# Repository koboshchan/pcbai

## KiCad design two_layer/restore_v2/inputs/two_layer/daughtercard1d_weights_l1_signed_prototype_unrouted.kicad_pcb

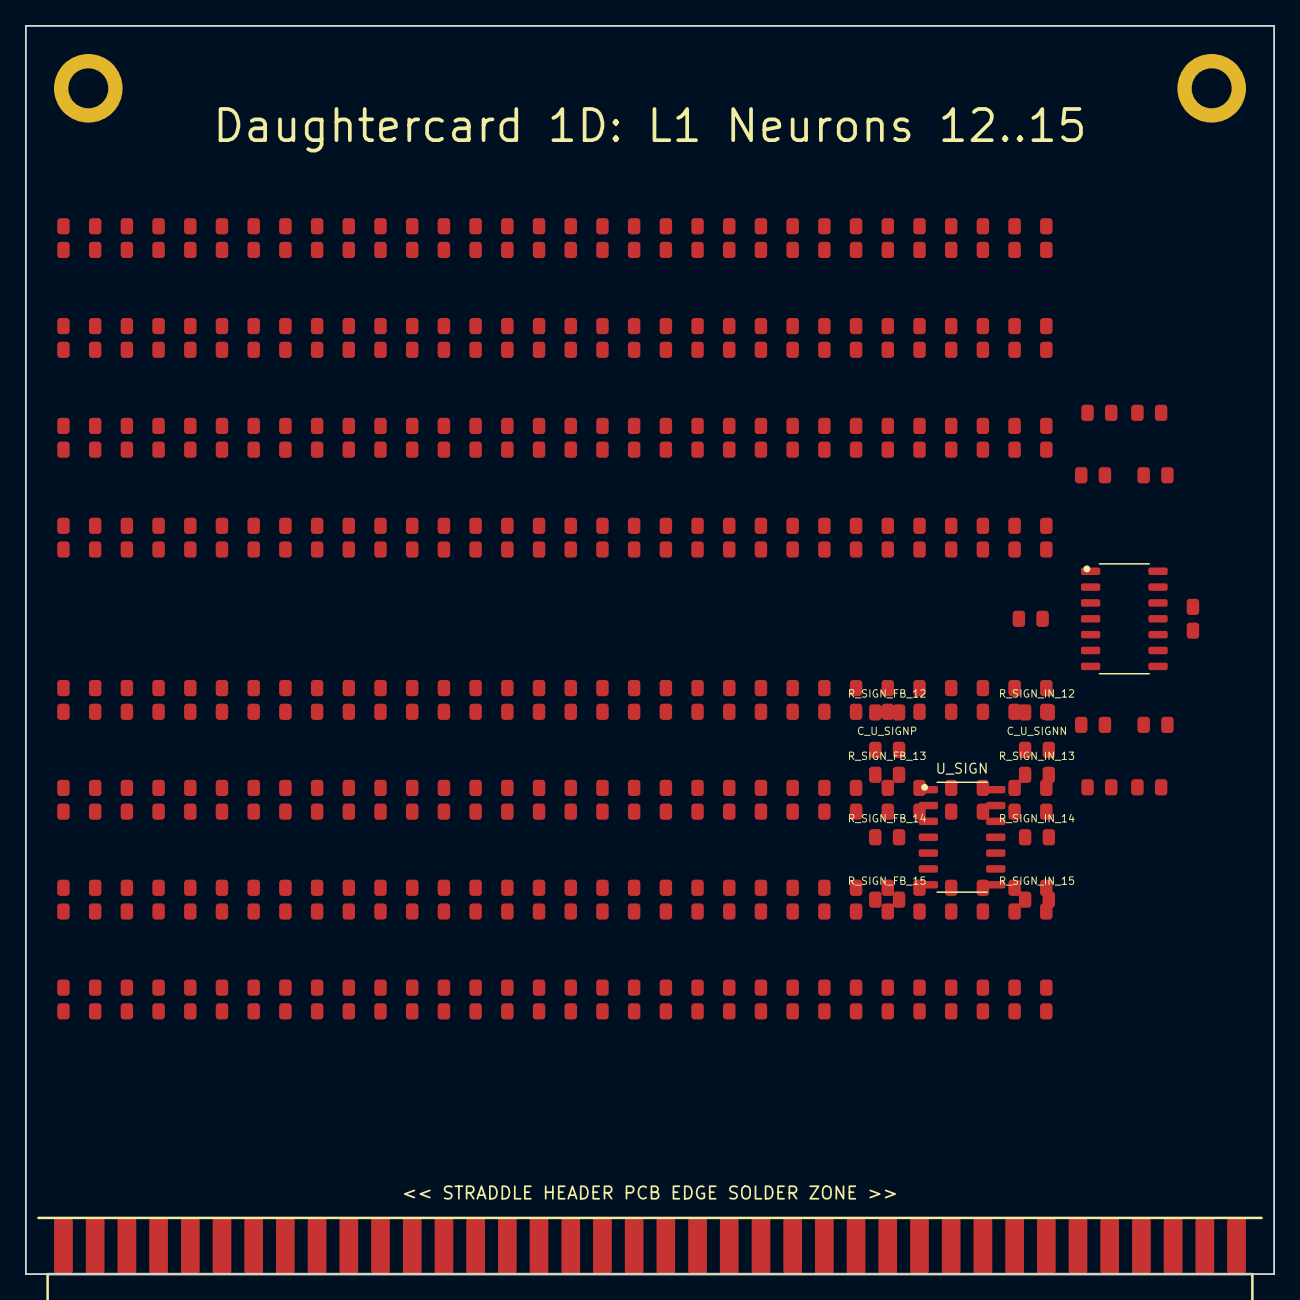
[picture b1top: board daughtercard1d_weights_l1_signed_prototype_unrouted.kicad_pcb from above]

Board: 2 copper layers, 100.0 x 100.0 mm, 281 parts (0 on the bottom side), 85 nets, no tracks yet.

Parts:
C_U1N, C_U1P: 0.1uF; C_0805_2012Metric
C_U_SIGNN: 0.1uF; C_0805_2012Metric
C_U_SIGNP: 0.1uF; C_0805_2012Metric
H1, H2: MountingHole; MountingHole_3.2mm_M3_Pad
J_STRADDLE_EDGE: PinHeader_2x38_Straddle; PinHeader_2x38_Straddle_P2.54mm
R1_0_0, R1_0_2, R1_8_2, R1_31_2, R1_56_2: 3.3k; R_0805_2012Metric
R1_0_1, R1_2_3, R1_4_0, R1_4_1, R1_7_0, R1_9_1, R1_10_1, R1_13_3, R1_18_2, R1_20_2, R1_22_0, R1_22_1, R1_26_3, R1_30_2, R1_31_1, R1_33_3, R1_35_3, R1_42_3, R1_44_3, R1_45_3, R1_52_3, R1_56_3, R1_62_3, R1_63_2: 51k; R_0805_2012Metric
R1_0_3, R1_1_1, R1_1_3, R1_5_1, R1_6_3, R1_12_3, R1_14_1, R1_16_3, R1_20_3, R1_27_3, R1_28_0, R1_30_3, R1_32_3, R1_37_3, R1_38_3, R1_40_1, R1_41_1, R1_43_3, R1_45_1, R1_48_3, R1_50_1, R1_50_3, R1_53_3, R1_54_3, R1_55_1, R1_57_1, R1_57_3, R1_58_1: 100k; R_0805_2012Metric
R1_1_0, R1_2_0, R1_10_0, R1_14_0, R1_15_0, R1_16_0, R1_17_2, R1_24_0, R1_24_2, R1_27_0, R1_37_2, R1_42_2, R1_50_0, R1_51_0, R1_57_0, R1_58_0, R1_62_0: 22k; R_0805_2012Metric
R1_1_2, R1_20_0, R1_48_0, R1_53_0, R1_55_0, R1_55_2, R1_57_2, R1_63_0: 12k; R_0805_2012Metric
R1_2_1, R1_3_3, R1_4_3, R1_5_2, R1_7_1, R1_7_2, R1_7_3, R1_9_0, R1_9_3, R1_12_1, R1_13_1, R1_15_1, R1_15_3, R1_17_0, R1_19_1, R1_21_3, R1_25_3, R1_29_1, R1_29_3, R1_32_1, R1_36_3, R1_37_1, R1_38_1, R1_41_3, R1_42_0, R1_42_1, R1_43_1, R1_43_2, R1_45_2, R1_46_3, R1_49_3, R1_55_3, R1_58_2, R1_59_1, R1_60_1, R1_61_3: 75k; R_0805_2012Metric
R1_2_2, R1_19_0, R1_25_2, R1_26_2, R1_32_0, R1_36_2, R1_60_2: 15k; R_0805_2012Metric
R1_3_0, R1_6_2, R1_8_0, R1_15_2, R1_31_0, R1_33_2, R1_35_0, R1_38_0, R1_41_2, R1_52_0, R1_59_0, R1_61_0: 18k; R_0805_2012Metric
R1_3_1, R1_6_1, R1_8_1, R1_10_3, R1_11_3, R1_12_2, R1_18_0, R1_18_1, R1_21_1, R1_21_2, R1_22_3, R1_23_1, R1_24_3, R1_25_1, R1_28_3, R1_40_0, R1_43_0, R1_46_0, R1_46_2, R1_47_3, R1_48_1, R1_49_1, R1_56_1, R1_58_3, R1_61_1: 200k; R_0805_2012Metric
R1_3_2, R1_5_0, R1_10_2, R1_11_1, R1_11_2, R1_12_0, R1_13_0, R1_20_1, R1_23_0, R1_26_0, R1_33_0, R1_37_0, R1_38_2, R1_61_2: 43k; R_0805_2012Metric
R1_4_2, R1_18_3, R1_19_3, R1_21_0, R1_30_1, R1_32_2, R1_33_1, R1_36_1, R1_39_1, R1_44_1, R1_53_1, R1_54_1, R1_63_3: 1M; R_0805_2012Metric
R1_5_3, R1_14_3, R1_19_2, R1_23_3, R1_34_1, R1_62_1, R1_63_1: 680k; R_0805_2012Metric
R1_6_0, R1_27_2, R1_35_2, R1_39_3, R1_44_0, R1_51_3, R1_60_3: 47k; R_0805_2012Metric
R1_8_3, R1_16_1, R1_17_1, R1_17_3, R1_27_1, R1_31_3, R1_40_3, R1_59_2, R1_59_3, R1_60_0: 300k; R_0805_2012Metric
R1_9_2, R1_11_0, R1_13_2, R1_14_2, R1_25_0, R1_28_2, R1_29_0, R1_29_2, R1_34_2, R1_36_0, R1_41_0, R1_44_2, R1_45_0, R1_49_0, R1_56_0: 33k; R_0805_2012Metric
R1_16_2, R1_39_2, R1_51_2: 5.6k; R_0805_2012Metric
R1_22_2, R1_35_1, R1_46_1, R1_52_1: 390k; R_0805_2012Metric
R1_23_2: 4.7k; R_0805_2012Metric
R1_24_1, R1_26_1, R1_28_1, R1_30_0, R1_47_1, R1_51_1: 470k; R_0805_2012Metric
R1_34_0, R1_39_0, R1_40_2, R1_62_2: 20k; R_0805_2012Metric
R1_34_3: DNP; R_0805_2012Metric
R1_47_0, R1_48_2, R1_54_0: 10k; R_0805_2012Metric
R1_47_2, R1_49_2, R1_50_2, R1_52_2, R1_53_2, R1_54_2: 7.5k; R_0805_2012Metric
R_SIGN_FB_12, R_SIGN_FB_13, R_SIGN_FB_14, R_SIGN_FB_15: 1.2k; R_0805_2012Metric
R_SIGN_IN_12, R_SIGN_IN_13, R_SIGN_IN_14, R_SIGN_IN_15: 1.2k; R_0805_2012Metric
Rb_N12: 51k; R_0805_2012Metric
Rb_N13: 300k; R_0805_2012Metric
Rb_N14: 18k; R_0805_2012Metric
Rb_N15: 390k; R_0805_2012Metric
Rf_N12, Rf_N13, Rf_N14, Rf_N15: 10k; R_0805_2012Metric
U1: TL074; SOIC-14_3.9x8.7mm_P1.27mm
U_SIGN: TL074; SOIC-14_3.9x8.7mm_P1.27mm

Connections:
+5V_REF: J_STRADDLE_EDGE.B35, Rb_N12.2, Rb_N14.2
+12V: C_U1P.2, C_U_SIGNP.1, J_STRADDLE_EDGE.B33, J_STRADDLE_EDGE.B34, U1.4, U_SIGN.4
-5V_REF: J_STRADDLE_EDGE.B36, Rb_N13.2, Rb_N15.2
-12V: C_U1N.1, C_U_SIGNN.1, J_STRADDLE_EDGE.B37, J_STRADDLE_EDGE.B38, U1.11, U_SIGN.11
GND: C_U1N.2, C_U1P.1, C_U_SIGNN.2, C_U_SIGNP.2, H1.1, H2.1, J_STRADDLE_EDGE.A37, J_STRADDLE_EDGE.A38, U1.3, U1.5, U1.10, U1.12, U_SIGN.3, U_SIGN.5, U_SIGN.10, U_SIGN.12
INV_N12: R1_7_0.2, R1_8_0.2, R1_15_0.2, R1_21_0.2, R1_22_0.2, R1_24_0.2, R1_25_0.2, R1_26_0.2, R1_27_0.2, R1_30_0.2, R1_33_0.2, R1_34_0.2, R1_35_0.2, R1_36_0.2, R1_39_0.2, R1_40_0.2, R1_41_0.2, R1_42_0.2, R1_43_0.2, R1_44_0.2, R1_45_0.2, R1_46_0.2, R1_48_0.2, R1_49_0.2, R1_50_0.2, R1_51_0.2, R1_52_0.2, R1_53_0.2, R1_54_0.2, R1_55_0.2, R1_57_0.2, R1_58_0.2, R1_59_0.2, R1_60_0.2, R1_61_0.2, R1_62_0.2, R1_63_0.2, R_SIGN_IN_12.2, Rb_N12.1, Rf_N12.2, U1.2
INV_N13: R1_8_1.2, R1_17_1.2, R1_26_1.2, R1_27_1.2, R1_30_1.2, R1_33_1.2, R1_34_1.2, R1_35_1.2, R1_39_1.2, R1_53_1.2, R1_54_1.2, R1_55_1.2, R1_62_1.2, R_SIGN_IN_13.2, Rb_N13.1, Rf_N13.2, U1.6
INV_N14: R1_1_2.2, R1_2_2.2, R1_3_2.2, R1_5_2.2, R1_6_2.2, R1_8_2.2, R1_9_2.2, R1_10_2.2, R1_11_2.2, R1_12_2.2, R1_13_2.2, R1_14_2.2, R1_15_2.2, R1_18_2.2, R1_20_2.2, R1_21_2.2, R1_24_2.2, R1_25_2.2, R1_26_2.2, R1_27_2.2, R1_28_2.2, R1_29_2.2, R1_30_2.2, R1_32_2.2, R1_33_2.2, R1_34_2.2, R1_35_2.2, R1_36_2.2, R1_37_2.2, R1_38_2.2, R1_43_2.2, R1_44_2.2, R1_45_2.2, R1_56_2.2, R1_57_2.2, R1_58_2.2, R1_59_2.2, R1_63_2.2, R_SIGN_IN_14.2, Rb_N14.1, Rf_N14.1, U1.9
INV_N15: R1_1_3.2, R1_8_3.2, R1_18_3.2, R1_19_3.2, R1_34_3.2, R1_47_3.2, R1_55_3.2, R1_63_3.2, R_SIGN_IN_15.2, Rb_N15.1, Rf_N15.1, U1.13
IN_0: J_STRADDLE_EDGE.A1, R1_0_0.1, R1_0_1.1, R1_0_2.1, R1_0_3.1
IN_1: J_STRADDLE_EDGE.A2, R1_1_0.1, R1_1_1.1, R1_1_2.1, R1_1_3.1
IN_2: J_STRADDLE_EDGE.A3, R1_2_0.1, R1_2_1.1, R1_2_2.1, R1_2_3.1
IN_3: J_STRADDLE_EDGE.A4, R1_3_0.1, R1_3_1.1, R1_3_2.1, R1_3_3.1
IN_4: J_STRADDLE_EDGE.A5, R1_4_0.1, R1_4_1.1, R1_4_2.1, R1_4_3.1
IN_5: J_STRADDLE_EDGE.A6, R1_5_0.1, R1_5_1.1, R1_5_2.1, R1_5_3.1
IN_6: J_STRADDLE_EDGE.A7, R1_6_0.1, R1_6_1.1, R1_6_2.1, R1_6_3.1
IN_7: J_STRADDLE_EDGE.A8, R1_7_0.1, R1_7_1.1, R1_7_2.1, R1_7_3.1
IN_8: J_STRADDLE_EDGE.A9, R1_8_0.1, R1_8_1.1, R1_8_2.1, R1_8_3.1
IN_9: J_STRADDLE_EDGE.A10, R1_9_0.1, R1_9_1.1, R1_9_2.1, R1_9_3.1
IN_10: J_STRADDLE_EDGE.A11, R1_10_0.1, R1_10_1.1, R1_10_2.1, R1_10_3.1
IN_11: J_STRADDLE_EDGE.A12, R1_11_0.1, R1_11_1.1, R1_11_2.1, R1_11_3.1
IN_12: J_STRADDLE_EDGE.A13, R1_12_0.1, R1_12_1.1, R1_12_2.1, R1_12_3.1
IN_13: J_STRADDLE_EDGE.A14, R1_13_0.1, R1_13_1.1, R1_13_2.1, R1_13_3.1
IN_14: J_STRADDLE_EDGE.A15, R1_14_0.1, R1_14_1.1, R1_14_2.1, R1_14_3.1
IN_15: J_STRADDLE_EDGE.A16, R1_15_0.1, R1_15_1.1, R1_15_2.1, R1_15_3.1
IN_16: J_STRADDLE_EDGE.A17, R1_16_0.1, R1_16_1.1, R1_16_2.1, R1_16_3.1
IN_17: J_STRADDLE_EDGE.A18, R1_17_0.1, R1_17_1.1, R1_17_2.1, R1_17_3.1
IN_18: J_STRADDLE_EDGE.A19, R1_18_0.1, R1_18_1.1, R1_18_2.1, R1_18_3.1
IN_19: J_STRADDLE_EDGE.A20, R1_19_0.1, R1_19_1.1, R1_19_2.1, R1_19_3.1
IN_20: J_STRADDLE_EDGE.A21, R1_20_0.1, R1_20_1.1, R1_20_2.1, R1_20_3.1
IN_21: J_STRADDLE_EDGE.A22, R1_21_0.1, R1_21_1.1, R1_21_2.1, R1_21_3.1
IN_22: J_STRADDLE_EDGE.A23, R1_22_0.1, R1_22_1.1, R1_22_2.1, R1_22_3.1
IN_23: J_STRADDLE_EDGE.A24, R1_23_0.1, R1_23_1.1, R1_23_2.1, R1_23_3.1
IN_24: J_STRADDLE_EDGE.A25, R1_24_0.1, R1_24_1.1, R1_24_2.1, R1_24_3.1
IN_25: J_STRADDLE_EDGE.A26, R1_25_0.1, R1_25_1.1, R1_25_2.1, R1_25_3.1
IN_26: J_STRADDLE_EDGE.A27, R1_26_0.1, R1_26_1.1, R1_26_2.1, R1_26_3.1
IN_27: J_STRADDLE_EDGE.A28, R1_27_0.1, R1_27_1.1, R1_27_2.1, R1_27_3.1
IN_28: J_STRADDLE_EDGE.A29, R1_28_0.1, R1_28_1.1, R1_28_2.1, R1_28_3.1
IN_29: J_STRADDLE_EDGE.A30, R1_29_0.1, R1_29_1.1, R1_29_2.1, R1_29_3.1
IN_30: J_STRADDLE_EDGE.A31, R1_30_0.1, R1_30_1.1, R1_30_2.1, R1_30_3.1
IN_31: J_STRADDLE_EDGE.A32, R1_31_0.1, R1_31_1.1, R1_31_2.1, R1_31_3.1
IN_32: J_STRADDLE_EDGE.B1, R1_32_0.1, R1_32_1.1, R1_32_2.1, R1_32_3.1
IN_33: J_STRADDLE_EDGE.B2, R1_33_0.1, R1_33_1.1, R1_33_2.1, R1_33_3.1
IN_34: J_STRADDLE_EDGE.B3, R1_34_0.1, R1_34_1.1, R1_34_2.1, R1_34_3.1
IN_35: J_STRADDLE_EDGE.B4, R1_35_0.1, R1_35_1.1, R1_35_2.1, R1_35_3.1
IN_36: J_STRADDLE_EDGE.B5, R1_36_0.1, R1_36_1.1, R1_36_2.1, R1_36_3.1
IN_37: J_STRADDLE_EDGE.B6, R1_37_0.1, R1_37_1.1, R1_37_2.1, R1_37_3.1
IN_38: J_STRADDLE_EDGE.B7, R1_38_0.1, R1_38_1.1, R1_38_2.1, R1_38_3.1
IN_39: J_STRADDLE_EDGE.B8, R1_39_0.1, R1_39_1.1, R1_39_2.1, R1_39_3.1
IN_40: J_STRADDLE_EDGE.B9, R1_40_0.1, R1_40_1.1, R1_40_2.1, R1_40_3.1
IN_41: J_STRADDLE_EDGE.B10, R1_41_0.1, R1_41_1.1, R1_41_2.1, R1_41_3.1
IN_42: J_STRADDLE_EDGE.B11, R1_42_0.1, R1_42_1.1, R1_42_2.1, R1_42_3.1
IN_43: J_STRADDLE_EDGE.B12, R1_43_0.1, R1_43_1.1, R1_43_2.1, R1_43_3.1
IN_44: J_STRADDLE_EDGE.B13, R1_44_0.1, R1_44_1.1, R1_44_2.1, R1_44_3.1
IN_45: J_STRADDLE_EDGE.B14, R1_45_0.1, R1_45_1.1, R1_45_2.1, R1_45_3.1
IN_46: J_STRADDLE_EDGE.B15, R1_46_0.1, R1_46_1.1, R1_46_2.1, R1_46_3.1
IN_47: J_STRADDLE_EDGE.B16, R1_47_0.1, R1_47_1.1, R1_47_2.1, R1_47_3.1
IN_48: J_STRADDLE_EDGE.B17, R1_48_0.1, R1_48_1.1, R1_48_2.1, R1_48_3.1
IN_49: J_STRADDLE_EDGE.B18, R1_49_0.1, R1_49_1.1, R1_49_2.1, R1_49_3.1
IN_50: J_STRADDLE_EDGE.B19, R1_50_0.1, R1_50_1.1, R1_50_2.1, R1_50_3.1
IN_51: J_STRADDLE_EDGE.B20, R1_51_0.1, R1_51_1.1, R1_51_2.1, R1_51_3.1
IN_52: J_STRADDLE_EDGE.B21, R1_52_0.1, R1_52_1.1, R1_52_2.1, R1_52_3.1
IN_53: J_STRADDLE_EDGE.B22, R1_53_0.1, R1_53_1.1, R1_53_2.1, R1_53_3.1
IN_54: J_STRADDLE_EDGE.B23, R1_54_0.1, R1_54_1.1, R1_54_2.1, R1_54_3.1
IN_55: J_STRADDLE_EDGE.B24, R1_55_0.1, R1_55_1.1, R1_55_2.1, R1_55_3.1
IN_56: J_STRADDLE_EDGE.B25, R1_56_0.1, R1_56_1.1, R1_56_2.1, R1_56_3.1
IN_57: J_STRADDLE_EDGE.B26, R1_57_0.1, R1_57_1.1, R1_57_2.1, R1_57_3.1
IN_58: J_STRADDLE_EDGE.B27, R1_58_0.1, R1_58_1.1, R1_58_2.1, R1_58_3.1
IN_59: J_STRADDLE_EDGE.B28, R1_59_0.1, R1_59_1.1, R1_59_2.1, R1_59_3.1
IN_60: J_STRADDLE_EDGE.B29, R1_60_0.1, R1_60_1.1, R1_60_2.1, R1_60_3.1
IN_61: J_STRADDLE_EDGE.B30, R1_61_0.1, R1_61_1.1, R1_61_2.1, R1_61_3.1
IN_62: J_STRADDLE_EDGE.B31, R1_62_0.1, R1_62_1.1, R1_62_2.1, R1_62_3.1
IN_63: J_STRADDLE_EDGE.B32, R1_63_0.1, R1_63_1.1, R1_63_2.1, R1_63_3.1
NEG_GROUP_12: R_SIGN_FB_12.1, R_SIGN_IN_12.1, U_SIGN.1
NEG_GROUP_13: R_SIGN_FB_13.1, R_SIGN_IN_13.1, U_SIGN.7
NEG_GROUP_14: R_SIGN_FB_14.1, R_SIGN_IN_14.1, U_SIGN.8
NEG_GROUP_15: R_SIGN_FB_15.1, R_SIGN_IN_15.1, U_SIGN.14
NEG_INV_12: R1_0_0.2, R1_1_0.2, R1_2_0.2, R1_3_0.2, R1_4_0.2, R1_5_0.2, R1_6_0.2, R1_9_0.2, R1_10_0.2, R1_11_0.2, R1_12_0.2, R1_13_0.2, R1_14_0.2, R1_16_0.2, R1_17_0.2, R1_18_0.2, R1_19_0.2, R1_20_0.2, R1_23_0.2, R1_28_0.2, R1_29_0.2, R1_31_0.2, R1_32_0.2, R1_37_0.2, R1_38_0.2, R1_47_0.2, R1_56_0.2, R_SIGN_FB_12.2, U_SIGN.2
NEG_INV_13: R1_0_1.2, R1_1_1.2, R1_2_1.2, R1_3_1.2, R1_4_1.2, R1_5_1.2, R1_6_1.2, R1_7_1.2, R1_9_1.2, R1_10_1.2, R1_11_1.2, R1_12_1.2, R1_13_1.2, R1_14_1.2, R1_15_1.2, R1_16_1.2, R1_18_1.2, R1_19_1.2, R1_20_1.2, R1_21_1.2, R1_22_1.2, R1_23_1.2, R1_24_1.2, R1_25_1.2, R1_28_1.2, R1_29_1.2, R1_31_1.2, R1_32_1.2, R1_36_1.2, R1_37_1.2, R1_38_1.2, R1_40_1.2, R1_41_1.2, R1_42_1.2, R1_43_1.2, R1_44_1.2, R1_45_1.2, R1_46_1.2, R1_47_1.2, R1_48_1.2, R1_49_1.2, R1_50_1.2, R1_51_1.2, R1_52_1.2, R1_56_1.2, R1_57_1.2, R1_58_1.2, R1_59_1.2, R1_60_1.2, R1_61_1.2, R1_63_1.2, R_SIGN_FB_13.2, U_SIGN.6
NEG_INV_14: R1_0_2.2, R1_4_2.2, R1_7_2.2, R1_16_2.2, R1_17_2.2, R1_19_2.2, R1_22_2.2, R1_23_2.2, R1_31_2.2, R1_39_2.2, R1_40_2.2, R1_41_2.2, R1_42_2.2, R1_46_2.2, R1_47_2.2, R1_48_2.2, R1_49_2.2, R1_50_2.2, R1_51_2.2, R1_52_2.2, R1_53_2.2, R1_54_2.2, R1_55_2.2, R1_60_2.2, R1_61_2.2, R1_62_2.2, R_SIGN_FB_14.2, U_SIGN.9
NEG_INV_15: R1_0_3.2, R1_2_3.2, R1_3_3.2, R1_4_3.2, R1_5_3.2, R1_6_3.2, R1_7_3.2, R1_9_3.2, R1_10_3.2, R1_11_3.2, R1_12_3.2, R1_13_3.2, R1_14_3.2, R1_15_3.2, R1_16_3.2, R1_17_3.2, R1_20_3.2, R1_21_3.2, R1_22_3.2, R1_23_3.2, R1_24_3.2, R1_25_3.2, R1_26_3.2, R1_27_3.2, R1_28_3.2, R1_29_3.2, R1_30_3.2, R1_31_3.2, R1_32_3.2, R1_33_3.2, R1_35_3.2, R1_36_3.2, R1_37_3.2, R1_38_3.2, R1_39_3.2, R1_40_3.2, R1_41_3.2, R1_42_3.2, R1_43_3.2, R1_44_3.2, R1_45_3.2, R1_46_3.2, R1_48_3.2, R1_49_3.2, R1_50_3.2, R1_51_3.2, R1_52_3.2, R1_53_3.2, R1_54_3.2, R1_56_3.2, R1_57_3.2, R1_58_3.2, R1_59_3.2, R1_60_3.2, R1_61_3.2, R1_62_3.2, R_SIGN_FB_15.2, U_SIGN.13
V_SUM_12: J_STRADDLE_EDGE.A33, Rf_N12.1, U1.1
V_SUM_13: J_STRADDLE_EDGE.A34, Rf_N13.1, U1.7
V_SUM_14: J_STRADDLE_EDGE.A35, Rf_N14.2, U1.8
V_SUM_15: J_STRADDLE_EDGE.A36, Rf_N15.2, U1.14

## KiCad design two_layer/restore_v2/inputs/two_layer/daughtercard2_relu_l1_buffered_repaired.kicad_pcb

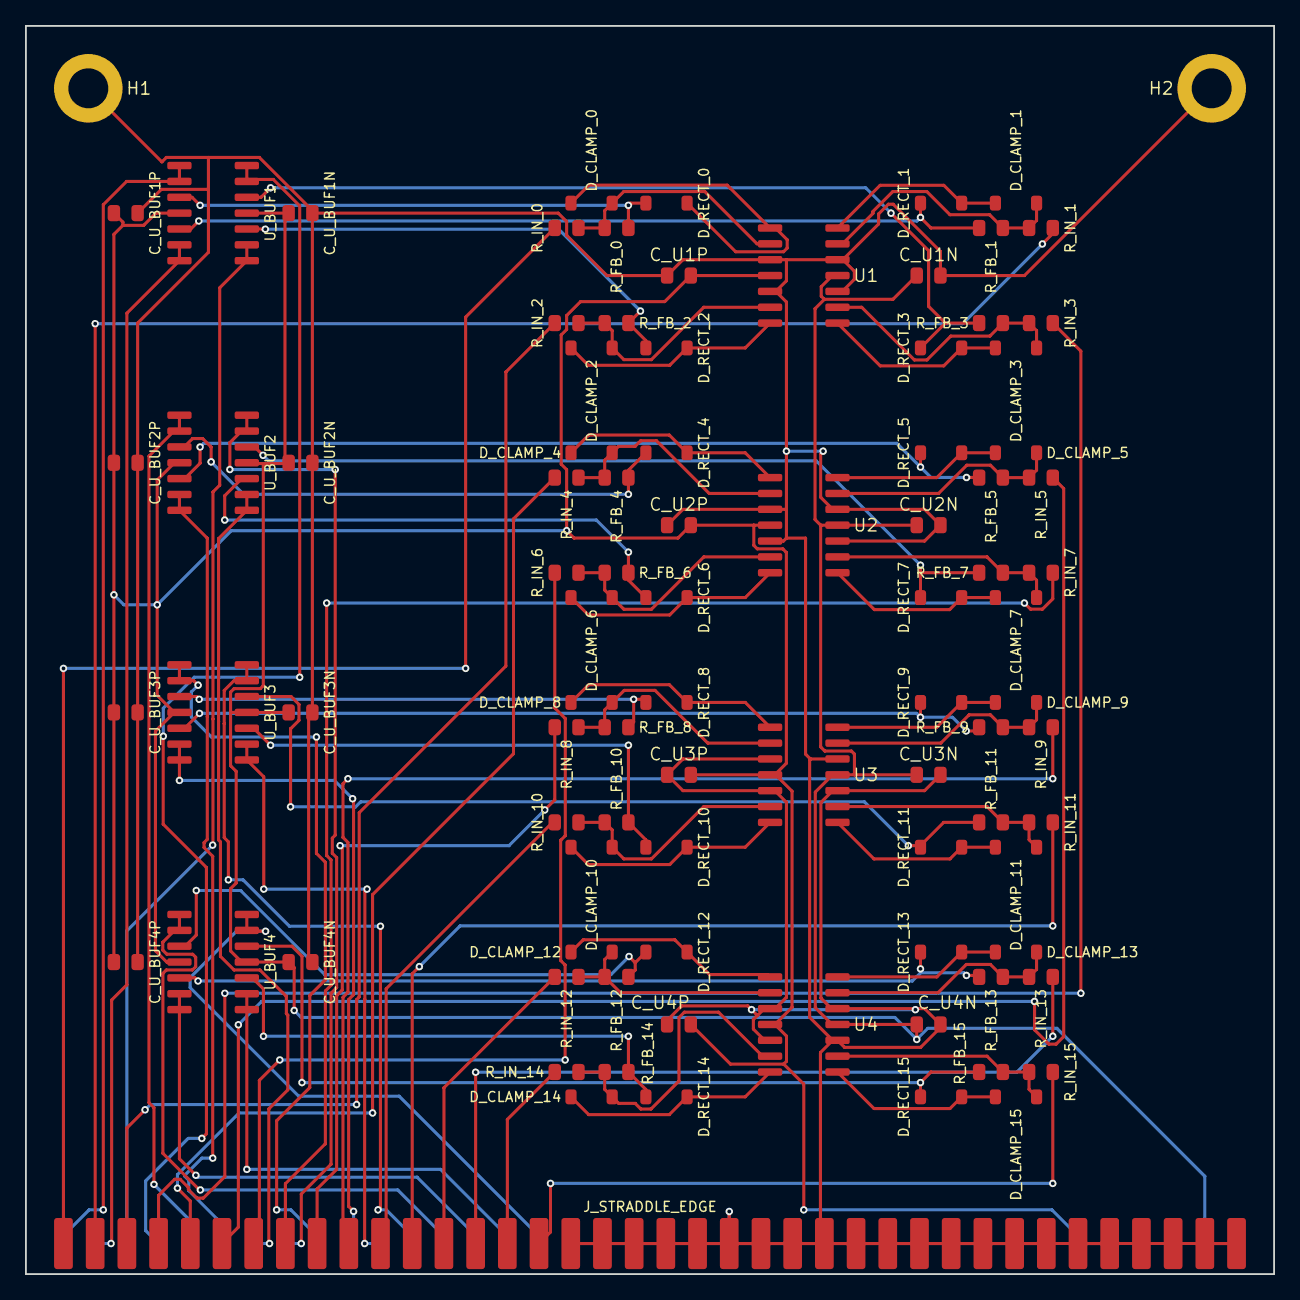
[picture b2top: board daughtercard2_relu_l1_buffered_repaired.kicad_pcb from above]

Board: 2 copper layers, 100.0 x 100.0 mm, 91 parts (0 on the bottom side), 83 nets.

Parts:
C_U1N, C_U1P, C_U2N, C_U2P, C_U3N, C_U3P, C_U4N, C_U4P: 0.1uF; C_0805_2012Metric
C_U_BUF1N, C_U_BUF1P, C_U_BUF2N, C_U_BUF2P, C_U_BUF3N, C_U_BUF3P, C_U_BUF4N, C_U_BUF4P: 0.1uF; C_0805_2012Metric
D_CLAMP_0, D_CLAMP_1, D_CLAMP_2, D_CLAMP_3, D_CLAMP_4, D_CLAMP_5, D_CLAMP_6, D_CLAMP_7, D_CLAMP_8, D_CLAMP_9, D_CLAMP_10, D_CLAMP_11, D_CLAMP_12, D_CLAMP_13, D_CLAMP_14, D_CLAMP_15: 1N4148W; D_SOD-123
D_RECT_0, D_RECT_1, D_RECT_2, D_RECT_3, D_RECT_4, D_RECT_5, D_RECT_6, D_RECT_7, D_RECT_8, D_RECT_9, D_RECT_10, D_RECT_11, D_RECT_12, D_RECT_13, D_RECT_14, D_RECT_15: 1N4148W; D_SOD-123
H1, H2: MountingHole; MountingHole_3.2mm_M3_Pad
J_STRADDLE_EDGE: PinHeader_2x38_Straddle; PinHeader_2x38_Straddle_P2.54mm
R_FB_0, R_FB_1, R_FB_2, R_FB_3, R_FB_4, R_FB_5, R_FB_6, R_FB_7, R_FB_8, R_FB_9, R_FB_10, R_FB_11, R_FB_12, R_FB_13, R_FB_14, R_FB_15: 10k; R_0805_2012Metric
R_IN_0, R_IN_1, R_IN_2, R_IN_3, R_IN_4, R_IN_5, R_IN_6, R_IN_7, R_IN_8, R_IN_9, R_IN_10, R_IN_11, R_IN_12, R_IN_13, R_IN_14, R_IN_15: 10k; R_0805_2012Metric
U1, U2, U3, U4: TL074; SOIC-14_3.9x8.7mm_P1.27mm
U_BUF1, U_BUF2, U_BUF3, U_BUF4: TL074; SOIC-14_3.9x8.7mm_P1.27mm

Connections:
+15V: C_U1P.2, C_U2P.2, C_U3P.2, C_U4P.2, C_U_BUF1P.1, C_U_BUF2P.1, C_U_BUF3P.1, C_U_BUF4P.1, J_STRADDLE_EDGE.B33, J_STRADDLE_EDGE.B34, U1.4, U2.4, U3.4, U4.4, U_BUF1.4, U_BUF2.4, U_BUF3.4, U_BUF4.4
-15V: C_U1N.1, C_U2N.1, C_U3N.1, C_U4N.1, C_U_BUF1N.1, C_U_BUF2N.1, C_U_BUF3N.1, C_U_BUF4N.1, J_STRADDLE_EDGE.B37, J_STRADDLE_EDGE.B38, U1.11, U2.11, U3.11, U4.11, U_BUF1.11, U_BUF2.11, U_BUF3.11, U_BUF4.11
ACT_0: J_STRADDLE_EDGE.B1, U_BUF1.1, U_BUF1.2
ACT_1: J_STRADDLE_EDGE.B2, U_BUF1.6, U_BUF1.7
ACT_2: J_STRADDLE_EDGE.B3, U_BUF1.8, U_BUF1.9
ACT_3: J_STRADDLE_EDGE.B4, U_BUF1.13, U_BUF1.14
ACT_4: J_STRADDLE_EDGE.B5, U_BUF2.1, U_BUF2.2
ACT_5: J_STRADDLE_EDGE.B6, U_BUF2.6, U_BUF2.7
ACT_6: J_STRADDLE_EDGE.B7, U_BUF2.8, U_BUF2.9
ACT_7: J_STRADDLE_EDGE.B8, U_BUF2.13, U_BUF2.14
ACT_8: J_STRADDLE_EDGE.B9, U_BUF3.1, U_BUF3.2
ACT_9: J_STRADDLE_EDGE.B10, U_BUF3.6, U_BUF3.7
ACT_10: J_STRADDLE_EDGE.B11, U_BUF3.8, U_BUF3.9
ACT_11: J_STRADDLE_EDGE.B12, U_BUF3.13, U_BUF3.14
ACT_12: J_STRADDLE_EDGE.B13, U_BUF4.1, U_BUF4.2
ACT_13: J_STRADDLE_EDGE.B14, U_BUF4.6, U_BUF4.7
ACT_14: J_STRADDLE_EDGE.B15, U_BUF4.8, U_BUF4.9
ACT_15: J_STRADDLE_EDGE.B16, U_BUF4.13, U_BUF4.14
GND: C_U1N.2, C_U1P.1, C_U2N.2, C_U2P.1, C_U3N.2, C_U3P.1, C_U4N.2, C_U4P.1, C_U_BUF1N.2, C_U_BUF1P.2, C_U_BUF2N.2, C_U_BUF2P.2, C_U_BUF3N.2, C_U_BUF3P.2, C_U_BUF4N.2, C_U_BUF4P.2, H1.1, H2.1, J_STRADDLE_EDGE.A17, J_STRADDLE_EDGE.A18, J_STRADDLE_EDGE.A19, J_STRADDLE_EDGE.A20, J_STRADDLE_EDGE.A21, J_STRADDLE_EDGE.A22, J_STRADDLE_EDGE.A23, J_STRADDLE_EDGE.A24, J_STRADDLE_EDGE.A25, J_STRADDLE_EDGE.A26, J_STRADDLE_EDGE.A27, J_STRADDLE_EDGE.A28, J_STRADDLE_EDGE.A29, J_STRADDLE_EDGE.A30, J_STRADDLE_EDGE.A31, J_STRADDLE_EDGE.A32, J_STRADDLE_EDGE.A33, J_STRADDLE_EDGE.A34, J_STRADDLE_EDGE.A35, J_STRADDLE_EDGE.A36, J_STRADDLE_EDGE.A37, J_STRADDLE_EDGE.A38, J_STRADDLE_EDGE.B17, J_STRADDLE_EDGE.B18, J_STRADDLE_EDGE.B19, J_STRADDLE_EDGE.B20, J_STRADDLE_EDGE.B21, J_STRADDLE_EDGE.B22, J_STRADDLE_EDGE.B23, J_STRADDLE_EDGE.B24, J_STRADDLE_EDGE.B25, J_STRADDLE_EDGE.B26, J_STRADDLE_EDGE.B27, J_STRADDLE_EDGE.B28, J_STRADDLE_EDGE.B29, J_STRADDLE_EDGE.B30, J_STRADDLE_EDGE.B31, J_STRADDLE_EDGE.B32, U1.3, U1.5, U1.10, U1.12, U2.3, U2.5, U2.10, U2.12, U3.3, U3.5, U3.10, U3.12, U4.3, U4.5, U4.10, U4.12
INV_RELU_0: D_CLAMP_0.2, R_FB_0.1, R_IN_0.2, U1.2
INV_RELU_1: D_CLAMP_1.2, R_FB_1.2, R_IN_1.1, U1.13
INV_RELU_2: D_CLAMP_2.2, R_FB_2.1, R_IN_2.2, U1.6
INV_RELU_3: D_CLAMP_3.2, R_FB_3.2, R_IN_3.1, U1.9
INV_RELU_4: D_CLAMP_4.2, R_FB_4.1, R_IN_4.2, U2.2
INV_RELU_5: D_CLAMP_5.2, R_FB_5.2, R_IN_5.1, U2.13
INV_RELU_6: D_CLAMP_6.2, R_FB_6.1, R_IN_6.2, U2.6
INV_RELU_7: D_CLAMP_7.2, R_FB_7.2, R_IN_7.1, U2.9
INV_RELU_8: D_CLAMP_8.2, R_FB_8.1, R_IN_8.2, U3.2
INV_RELU_9: D_CLAMP_9.2, R_FB_9.2, R_IN_9.1, U3.13
INV_RELU_10: D_CLAMP_10.2, R_FB_10.1, R_IN_10.2, U3.6
INV_RELU_11: D_CLAMP_11.2, R_FB_11.2, R_IN_11.1, U3.9
INV_RELU_12: D_CLAMP_12.2, R_FB_12.1, R_IN_12.2, U4.2
INV_RELU_13: D_CLAMP_13.2, R_FB_13.2, R_IN_13.1, U4.13
INV_RELU_14: D_CLAMP_14.2, R_FB_14.1, R_IN_14.2, U4.6
INV_RELU_15: D_CLAMP_15.2, R_FB_15.2, R_IN_15.1, U4.9
OP_OUT_0: D_CLAMP_0.1, D_RECT_0.2, U1.1
OP_OUT_1: D_CLAMP_1.1, D_RECT_1.2, U1.14
OP_OUT_2: D_CLAMP_2.1, D_RECT_2.2, U1.7
OP_OUT_3: D_CLAMP_3.1, D_RECT_3.2, U1.8
OP_OUT_4: D_CLAMP_4.1, D_RECT_4.2, U2.1
OP_OUT_5: D_CLAMP_5.1, D_RECT_5.2, U2.14
OP_OUT_6: D_CLAMP_6.1, D_RECT_6.2, U2.7
OP_OUT_7: D_CLAMP_7.1, D_RECT_7.2, U2.8
OP_OUT_8: D_CLAMP_8.1, D_RECT_8.2, U3.1
OP_OUT_9: D_CLAMP_9.1, D_RECT_9.2, U3.14
OP_OUT_10: D_CLAMP_10.1, D_RECT_10.2, U3.7
OP_OUT_11: D_CLAMP_11.1, D_RECT_11.2, U3.8
OP_OUT_12: D_CLAMP_12.1, D_RECT_12.2, U4.1
OP_OUT_13: D_CLAMP_13.1, D_RECT_13.2, U4.14
OP_OUT_14: D_CLAMP_14.1, D_RECT_14.2, U4.7
OP_OUT_15: D_CLAMP_15.1, D_RECT_15.2, U4.8
RECT_0: D_RECT_0.1, R_FB_0.2, U_BUF1.3
RECT_1: D_RECT_1.1, R_FB_1.1, U_BUF1.5
RECT_2: D_RECT_2.1, R_FB_2.2, U_BUF1.10
RECT_3: D_RECT_3.1, R_FB_3.1, U_BUF1.12
RECT_4: D_RECT_4.1, R_FB_4.2, U_BUF2.3
RECT_5: D_RECT_5.1, R_FB_5.1, U_BUF2.5
RECT_6: D_RECT_6.1, R_FB_6.2, U_BUF2.10
RECT_7: D_RECT_7.1, R_FB_7.1, U_BUF2.12
RECT_8: D_RECT_8.1, R_FB_8.2, U_BUF3.3
RECT_9: D_RECT_9.1, R_FB_9.1, U_BUF3.5
RECT_10: D_RECT_10.1, R_FB_10.2, U_BUF3.10
RECT_11: D_RECT_11.1, R_FB_11.1, U_BUF3.12
RECT_12: D_RECT_12.1, R_FB_12.2, U_BUF4.3
RECT_13: D_RECT_13.1, R_FB_13.1, U_BUF4.5
RECT_14: D_RECT_14.1, R_FB_14.2, U_BUF4.10
RECT_15: D_RECT_15.1, R_FB_15.1, U_BUF4.12
V_SUM_0: J_STRADDLE_EDGE.A1, R_IN_0.1
V_SUM_1: J_STRADDLE_EDGE.A2, R_IN_1.2
V_SUM_2: J_STRADDLE_EDGE.A3, R_IN_2.1
V_SUM_3: J_STRADDLE_EDGE.A4, R_IN_3.2
V_SUM_4: J_STRADDLE_EDGE.A5, R_IN_4.1
V_SUM_5: J_STRADDLE_EDGE.A6, R_IN_5.2
V_SUM_6: J_STRADDLE_EDGE.A7, R_IN_6.1
V_SUM_7: J_STRADDLE_EDGE.A8, R_IN_7.2
V_SUM_8: J_STRADDLE_EDGE.A9, R_IN_8.1
V_SUM_9: J_STRADDLE_EDGE.A10, R_IN_9.2
V_SUM_10: J_STRADDLE_EDGE.A11, R_IN_10.1
V_SUM_11: J_STRADDLE_EDGE.A12, R_IN_11.2
V_SUM_12: J_STRADDLE_EDGE.A13, R_IN_12.1
V_SUM_13: J_STRADDLE_EDGE.A14, R_IN_13.2
V_SUM_14: J_STRADDLE_EDGE.A15, R_IN_14.1
V_SUM_15: J_STRADDLE_EDGE.A16, R_IN_15.2

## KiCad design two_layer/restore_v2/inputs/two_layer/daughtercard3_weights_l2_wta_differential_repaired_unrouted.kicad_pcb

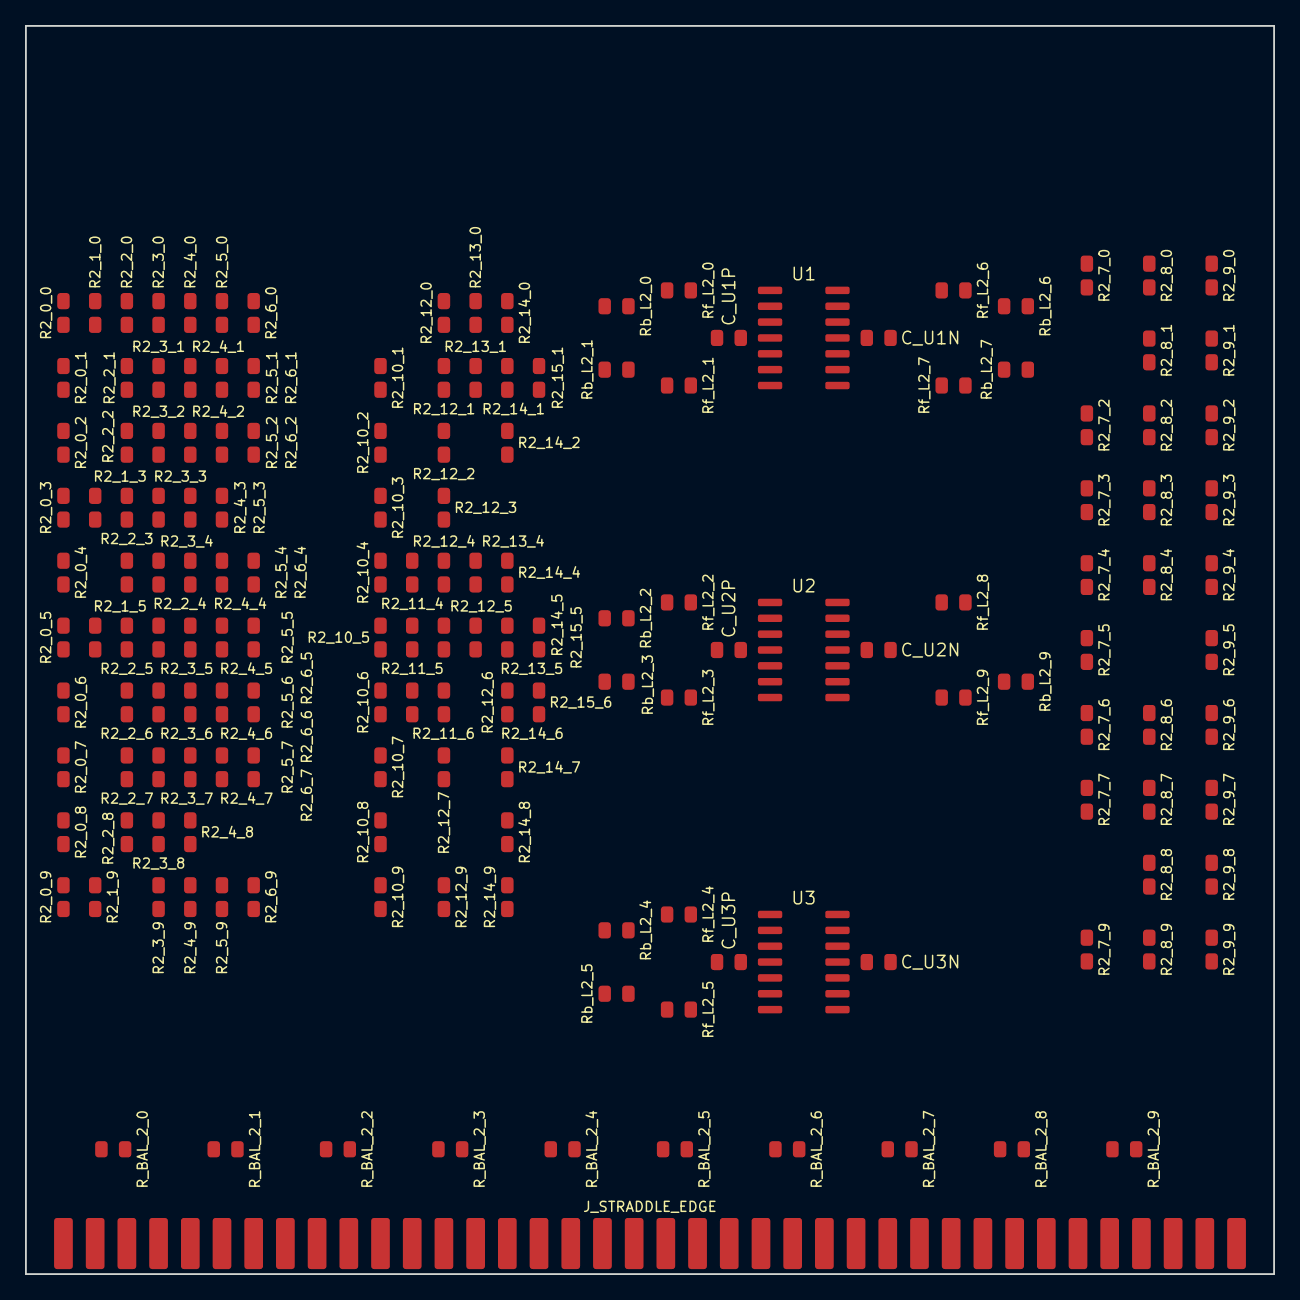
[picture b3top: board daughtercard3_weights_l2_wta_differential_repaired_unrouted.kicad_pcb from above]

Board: 2 copper layers, 100.0 x 100.0 mm, 163 parts (0 on the bottom side), 52 nets, no tracks yet.

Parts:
C_U1N, C_U1P, C_U2N, C_U2P, C_U3N, C_U3P: 0.1uF; C_0805_2012Metric
J_STRADDLE_EDGE: PinHeader_2x38_Straddle; PinHeader_2x38_Straddle_P2.54mm
R2_0_0, R2_3_2, R2_8_3, R2_9_1, R2_10_6: 91k; R_0805_2012Metric
R2_0_1, R2_3_0, R2_6_5, R2_7_4, R2_9_0, R2_14_1: 100k; R_0805_2012Metric
R2_0_2: 1.6M; R_0805_2012Metric
R2_0_3, R2_1_3, R2_5_4, R2_6_2, R2_7_6, R2_10_5, R2_10_8, R2_13_0, R2_14_0: 220k; R_0805_2012Metric
R2_0_4, R2_2_7, R2_5_3, R2_7_3, R2_8_6, R2_9_3, R2_13_5: 270k; R_0805_2012Metric
R2_0_5, R2_0_6, R2_5_0: 56k; R_0805_2012Metric
R2_0_7, R2_3_5: 470k; R_0805_2012Metric
R2_0_8, R2_1_9, R2_5_5, R2_5_9, R2_9_2, R2_9_4, R2_9_8, R2_10_7, R2_11_4, R2_11_6, R2_12_6: 180k; R_0805_2012Metric
R2_0_9, R2_2_2, R2_4_5, R2_4_6, R2_8_9, R2_12_5, R2_14_9: 300k; R_0805_2012Metric
R2_1_0, R2_2_3, R2_2_4, R2_8_0, R2_10_3, R2_11_5, R2_14_7, R2_15_5: 240k; R_0805_2012Metric
R2_1_5, R2_5_1: 82k; R_0805_2012Metric
R2_2_0, R2_10_9, R2_14_8: 110k; R_0805_2012Metric
R2_2_1: 51k; R_0805_2012Metric
R2_2_5, R2_3_3, R2_3_7, R2_15_6: 360k; R_0805_2012Metric
R2_2_6, R2_4_9: 430k; R_0805_2012Metric
R2_2_8: 5.1M; R_0805_2012Metric
R2_3_1, R2_6_9, R2_7_7, R2_9_9, R2_10_2, R2_13_4: 150k; R_0805_2012Metric
R2_3_4, R2_3_9, R2_5_2, R2_14_4: 130k; R_0805_2012Metric
R2_3_6, R2_5_6, R2_6_4, R2_7_2, R2_7_5, R2_10_1: 68k; R_0805_2012Metric
R2_3_8, R2_5_7, R2_6_0, R2_6_6, R2_8_2, R2_12_1, R2_12_4, R2_14_6: 200k; R_0805_2012Metric
R2_4_0, R2_9_5: 1M; R_0805_2012Metric
R2_4_1, R2_4_4, R2_8_8: 120k; R_0805_2012Metric
R2_4_2: 680k; R_0805_2012Metric
R2_4_3, R2_14_2: 750k; R_0805_2012Metric
R2_4_7, R2_12_3: 390k; R_0805_2012Metric
R2_4_8: 62k; R_0805_2012Metric
R2_6_1, R2_12_7: 43k; R_0805_2012Metric
R2_6_7, R2_8_7: 330k; R_0805_2012Metric
R2_7_0, R2_7_9: 75k; R_0805_2012Metric
R2_8_1, R2_12_9, R2_15_1: 160k; R_0805_2012Metric
R2_8_4, R2_9_6, R2_9_7: 620k; R_0805_2012Metric
R2_10_4: 33k; R_0805_2012Metric
R2_12_0: 510k; R_0805_2012Metric
R2_12_2: 1.1M; R_0805_2012Metric
R2_13_1: 820k; R_0805_2012Metric
R2_14_5: 2.7M; R_0805_2012Metric
R_BAL_2_0: 14.7k; R_0805_2012Metric
R_BAL_2_1: 24.9k; R_0805_2012Metric
R_BAL_2_2: 35.7k; R_0805_2012Metric
R_BAL_2_3: 61.9k; R_0805_2012Metric
R_BAL_2_4: 17.4k; R_0805_2012Metric
R_BAL_2_5: 28k; R_0805_2012Metric
R_BAL_2_6: 14.3k; R_0805_2012Metric
R_BAL_2_7: 34k; R_0805_2012Metric
R_BAL_2_8: 21k; R_0805_2012Metric
R_BAL_2_9: 18.2k; R_0805_2012Metric
Rb_L2_0: 270k; R_0805_2012Metric
Rb_L2_1, Rb_L2_3: 160k; R_0805_2012Metric
Rb_L2_2, Rb_L2_4: 560k; R_0805_2012Metric
Rb_L2_5: 2M; R_0805_2012Metric
Rb_L2_6: 240k; R_0805_2012Metric
Rb_L2_7: 3.9M; R_0805_2012Metric
Rb_L2_9: 360k; R_0805_2012Metric
Rf_L2_0, Rf_L2_1, Rf_L2_2, Rf_L2_3, Rf_L2_4, Rf_L2_5, Rf_L2_6, Rf_L2_7, Rf_L2_8, Rf_L2_9: 100k; R_0805_2012Metric
U1, U2, U3: TL074; SOIC-14_3.9x8.7mm_P1.27mm

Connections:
+5V_REF: J_STRADDLE_EDGE.B35, Rb_L2_0.1, Rb_L2_1.1, Rb_L2_2.1, Rb_L2_3.1, Rb_L2_4.1, Rb_L2_5.1, Rb_L2_6.1, Rb_L2_7.1, Rb_L2_9.1
+15V: C_U1P.2, C_U2P.2, C_U3P.2, J_STRADDLE_EDGE.B33, J_STRADDLE_EDGE.B34, U1.4, U2.4, U3.4
-15V: C_U1N.1, C_U2N.1, C_U3N.1, J_STRADDLE_EDGE.B37, J_STRADDLE_EDGE.B38, U1.11, U2.11, U3.11
ACT_0: J_STRADDLE_EDGE.A1, R2_0_0.1, R2_0_1.1, R2_0_2.1, R2_0_3.1, R2_0_4.1, R2_0_5.1, R2_0_6.1, R2_0_7.1, R2_0_8.1, R2_0_9.1
ACT_1: J_STRADDLE_EDGE.A2, R2_1_0.1, R2_1_3.1, R2_1_5.1, R2_1_9.1
ACT_2: J_STRADDLE_EDGE.A3, R2_2_0.1, R2_2_1.1, R2_2_2.1, R2_2_3.1, R2_2_4.1, R2_2_5.1, R2_2_6.1, R2_2_7.1, R2_2_8.1
ACT_3: J_STRADDLE_EDGE.A4, R2_3_0.1, R2_3_1.1, R2_3_2.1, R2_3_3.1, R2_3_4.1, R2_3_5.1, R2_3_6.1, R2_3_7.1, R2_3_8.1, R2_3_9.1
ACT_4: J_STRADDLE_EDGE.A5, R2_4_0.1, R2_4_1.1, R2_4_2.1, R2_4_3.1, R2_4_4.1, R2_4_5.1, R2_4_6.1, R2_4_7.1, R2_4_8.1, R2_4_9.1
ACT_5: J_STRADDLE_EDGE.A6, R2_5_0.1, R2_5_1.1, R2_5_2.1, R2_5_3.1, R2_5_4.1, R2_5_5.1, R2_5_6.1, R2_5_7.1, R2_5_9.1
ACT_6: J_STRADDLE_EDGE.A7, R2_6_0.1, R2_6_1.1, R2_6_2.1, R2_6_4.1, R2_6_5.1, R2_6_6.1, R2_6_7.1, R2_6_9.1
ACT_7: J_STRADDLE_EDGE.A8, R2_7_0.1, R2_7_2.1, R2_7_3.1, R2_7_4.1, R2_7_5.1, R2_7_6.1, R2_7_7.1, R2_7_9.1
ACT_8: J_STRADDLE_EDGE.A9, R2_8_0.1, R2_8_1.1, R2_8_2.1, R2_8_3.1, R2_8_4.1, R2_8_6.1, R2_8_7.1, R2_8_8.1, R2_8_9.1
ACT_9: J_STRADDLE_EDGE.A10, R2_9_0.1, R2_9_1.1, R2_9_2.1, R2_9_3.1, R2_9_4.1, R2_9_5.1, R2_9_6.1, R2_9_7.1, R2_9_8.1, R2_9_9.1
ACT_10: J_STRADDLE_EDGE.A11, R2_10_1.1, R2_10_2.1, R2_10_3.1, R2_10_4.1, R2_10_5.1, R2_10_6.1, R2_10_7.1, R2_10_8.1, R2_10_9.1
ACT_11: J_STRADDLE_EDGE.A12, R2_11_4.1, R2_11_5.1, R2_11_6.1
ACT_12: J_STRADDLE_EDGE.A13, R2_12_0.1, R2_12_1.1, R2_12_2.1, R2_12_3.1, R2_12_4.1, R2_12_5.1, R2_12_6.1, R2_12_7.1, R2_12_9.1
ACT_13: J_STRADDLE_EDGE.A14, R2_13_0.1, R2_13_1.1, R2_13_4.1, R2_13_5.1
ACT_14: J_STRADDLE_EDGE.A15, R2_14_0.1, R2_14_1.1, R2_14_2.1, R2_14_4.1, R2_14_5.1, R2_14_6.1, R2_14_7.1, R2_14_8.1, R2_14_9.1
ACT_15: J_STRADDLE_EDGE.A16, R2_15_1.1, R2_15_5.1, R2_15_6.1
GND: C_U1N.2, C_U1P.1, C_U2N.2, C_U2P.1, C_U3N.2, C_U3P.1, J_STRADDLE_EDGE.A17, J_STRADDLE_EDGE.A18, J_STRADDLE_EDGE.A19, J_STRADDLE_EDGE.A20, J_STRADDLE_EDGE.A21, J_STRADDLE_EDGE.A22, J_STRADDLE_EDGE.A23, J_STRADDLE_EDGE.A24, J_STRADDLE_EDGE.A25, J_STRADDLE_EDGE.A26, J_STRADDLE_EDGE.A27, J_STRADDLE_EDGE.A28, J_STRADDLE_EDGE.A29, J_STRADDLE_EDGE.A30, J_STRADDLE_EDGE.A31, J_STRADDLE_EDGE.A32, J_STRADDLE_EDGE.A33, J_STRADDLE_EDGE.A34, J_STRADDLE_EDGE.A35, J_STRADDLE_EDGE.A36, J_STRADDLE_EDGE.A37, J_STRADDLE_EDGE.A38, J_STRADDLE_EDGE.B11, J_STRADDLE_EDGE.B12, J_STRADDLE_EDGE.B13, J_STRADDLE_EDGE.B14, J_STRADDLE_EDGE.B15, J_STRADDLE_EDGE.B16, J_STRADDLE_EDGE.B17, J_STRADDLE_EDGE.B18, J_STRADDLE_EDGE.B19, J_STRADDLE_EDGE.B20, J_STRADDLE_EDGE.B21, J_STRADDLE_EDGE.B22, J_STRADDLE_EDGE.B23, J_STRADDLE_EDGE.B24, J_STRADDLE_EDGE.B25, J_STRADDLE_EDGE.B26, J_STRADDLE_EDGE.B27, J_STRADDLE_EDGE.B28, J_STRADDLE_EDGE.B29, J_STRADDLE_EDGE.B30, J_STRADDLE_EDGE.B31, J_STRADDLE_EDGE.B32, R_BAL_2_0.2, R_BAL_2_1.2, R_BAL_2_2.2, R_BAL_2_3.2, R_BAL_2_4.2, R_BAL_2_5.2, R_BAL_2_6.2, R_BAL_2_7.2, R_BAL_2_8.2, R_BAL_2_9.2, U3.10, U3.12
INV_L2_0: R2_0_0.2, R2_3_0.2, R2_4_0.2, R2_5_0.2, R2_6_0.2, R2_7_0.2, R2_9_0.2, R2_12_0.2, R2_13_0.2, R2_14_0.2, Rf_L2_0.1, U1.2
INV_L2_1: R2_2_1.2, R2_3_1.2, R2_6_1.2, R2_8_1.2, R2_10_1.2, R2_12_1.2, R2_14_1.2, Rf_L2_1.1, U1.6
INV_L2_2: R2_0_2.2, R2_2_2.2, R2_5_2.2, R2_6_2.2, R2_7_2.2, R2_8_2.2, R2_9_2.2, Rf_L2_2.1, U2.2
INV_L2_3: R2_1_3.2, R2_4_3.2, R2_8_3.2, R2_9_3.2, R2_12_3.2, Rb_L2_3.2, Rf_L2_3.1, U2.6
INV_L2_4: R2_0_4.2, R2_2_4.2, R2_3_4.2, R2_4_4.2, R2_6_4.2, R2_7_4.2, R2_8_4.2, R2_10_4.2, Rb_L2_4.2, Rf_L2_4.1, U3.2
INV_L2_5: R2_0_5.2, R2_1_5.2, R2_3_5.2, R2_5_5.2, R2_10_5.2, R2_11_5.2, R2_12_5.2, R2_13_5.2, R2_15_5.2, Rb_L2_5.2, Rf_L2_5.1, U3.6
INV_L2_6: R2_0_6.2, R2_2_6.2, R2_3_6.2, R2_4_6.2, R2_5_6.2, R2_8_6.2, R2_10_6.2, R2_11_6.2, R2_14_6.2, R2_15_6.2, Rf_L2_6.1, U1.13
INV_L2_7: R2_2_7.2, R2_5_7.2, R2_6_7.2, R2_7_7.2, R2_12_7.2, Rf_L2_7.1, U1.9
INV_L2_8: R2_0_8.2, R2_3_8.2, R2_4_8.2, R2_9_8.2, R2_10_8.2, R2_14_8.2, Rf_L2_8.1, U2.13
INV_L2_9: R2_1_9.2, R2_3_9.2, R2_4_9.2, R2_6_9.2, R2_7_9.2, R2_9_9.2, R2_10_9.2, R2_12_9.2, Rb_L2_9.2, Rf_L2_9.1, U2.9
NC_U3_8: U3.8, U3.9
NC_U3_14: U3.13, U3.14
POS_L2_0: R2_1_0.2, R2_2_0.2, R2_8_0.2, R_BAL_2_0.1, Rb_L2_0.2, U1.3
POS_L2_1: R2_0_1.2, R2_4_1.2, R2_5_1.2, R2_9_1.2, R2_13_1.2, R2_15_1.2, R_BAL_2_1.1, Rb_L2_1.2, U1.5
POS_L2_2: R2_3_2.2, R2_4_2.2, R2_10_2.2, R2_12_2.2, R2_14_2.2, R_BAL_2_2.1, Rb_L2_2.2, U2.3
POS_L2_3: R2_0_3.2, R2_2_3.2, R2_3_3.2, R2_5_3.2, R2_7_3.2, R2_10_3.2, R_BAL_2_3.1, U2.5
POS_L2_4: R2_5_4.2, R2_9_4.2, R2_11_4.2, R2_12_4.2, R2_13_4.2, R2_14_4.2, R_BAL_2_4.1, U3.3
POS_L2_5: R2_2_5.2, R2_4_5.2, R2_6_5.2, R2_7_5.2, R2_9_5.2, R2_14_5.2, R_BAL_2_5.1, U3.5
POS_L2_6: R2_6_6.2, R2_7_6.2, R2_9_6.2, R2_12_6.2, R_BAL_2_6.1, Rb_L2_6.2, U1.12
POS_L2_7: R2_0_7.2, R2_3_7.2, R2_4_7.2, R2_8_7.2, R2_9_7.2, R2_10_7.2, R2_14_7.2, R_BAL_2_7.1, Rb_L2_7.2, U1.10
POS_L2_8: R2_2_8.2, R2_8_8.2, R_BAL_2_8.1, U2.12
POS_L2_9: R2_0_9.2, R2_5_9.2, R2_8_9.2, R2_14_9.2, R_BAL_2_9.1, U2.10
SCORE_0: J_STRADDLE_EDGE.B1, Rf_L2_0.2, U1.1
SCORE_1: J_STRADDLE_EDGE.B2, Rf_L2_1.2, U1.7
SCORE_2: J_STRADDLE_EDGE.B3, Rf_L2_2.2, U2.1
SCORE_3: J_STRADDLE_EDGE.B4, Rf_L2_3.2, U2.7
SCORE_4: J_STRADDLE_EDGE.B5, Rf_L2_4.2, U3.1
SCORE_5: J_STRADDLE_EDGE.B6, Rf_L2_5.2, U3.7
SCORE_6: J_STRADDLE_EDGE.B7, Rf_L2_6.2, U1.14
SCORE_7: J_STRADDLE_EDGE.B8, Rf_L2_7.2, U1.8
SCORE_8: J_STRADDLE_EDGE.B9, Rf_L2_8.2, U2.14
SCORE_9: J_STRADDLE_EDGE.B10, Rf_L2_9.2, U2.8
